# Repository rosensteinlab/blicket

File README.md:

### An Open-Source Blicket Detector for Cognitive Science Research

Hatem Mohamed<sup>1</sup>, Gabriella Modesti<sup>2</sup>, David M. Sobel<sup>2</sup>, and Jacob K. Rosenstein<sup>1</sup>

<sup>1</sup> School of Engineering, Brown University, Providence, RI

<sup>2</sup> Department of Cognitive and Psychological Sciences, Brown University, Providence, RI

This project presents a practical, reprogrammable Blicket Detector designed to support cognitive psychology experiments that investigate causal reasoning in young children. The device combines an Arduino-based microcontroller, an RF remote module, LED strips, switches, and a translucent window to deliver flexible, interactive feedback through light and sound. The design allows different behaviors—such as multi-color illumination and buzzer activation—to be easily reconfigured using existing Arduino libraries, making it simple to adapt to various experimental needs. Powered by a portable power bank, the system features a modular PCB layout that simplifies assembly and maintenance while keeping power consumption low. By providing an intuitive, hands-on way for children to explore cause-and-effect relationships, this Blicket Detector offers researchers a reliable, customizable platform for replicating and extending classic experiments on early cognitive development.

--------------------

All data, source code, and supporting files are available on the GitHub repository:
https://github.com/rosensteinlab/blicket 

If you use or refer to this design, please cite it as:

Hatem Mohamed, Gabriella Modesti, David M. Sobel, and Jacob K. Rosenstein. “An Open-Source Blicket Detector for Cognitive Science Research.” School of Engineering and Department of Cognitive and Psychological Sciences, Brown University, 2025. Available at: https://github.com/rosensteinlab/blicket. DOI: 10.5281/zenodo.15880720

--------------------

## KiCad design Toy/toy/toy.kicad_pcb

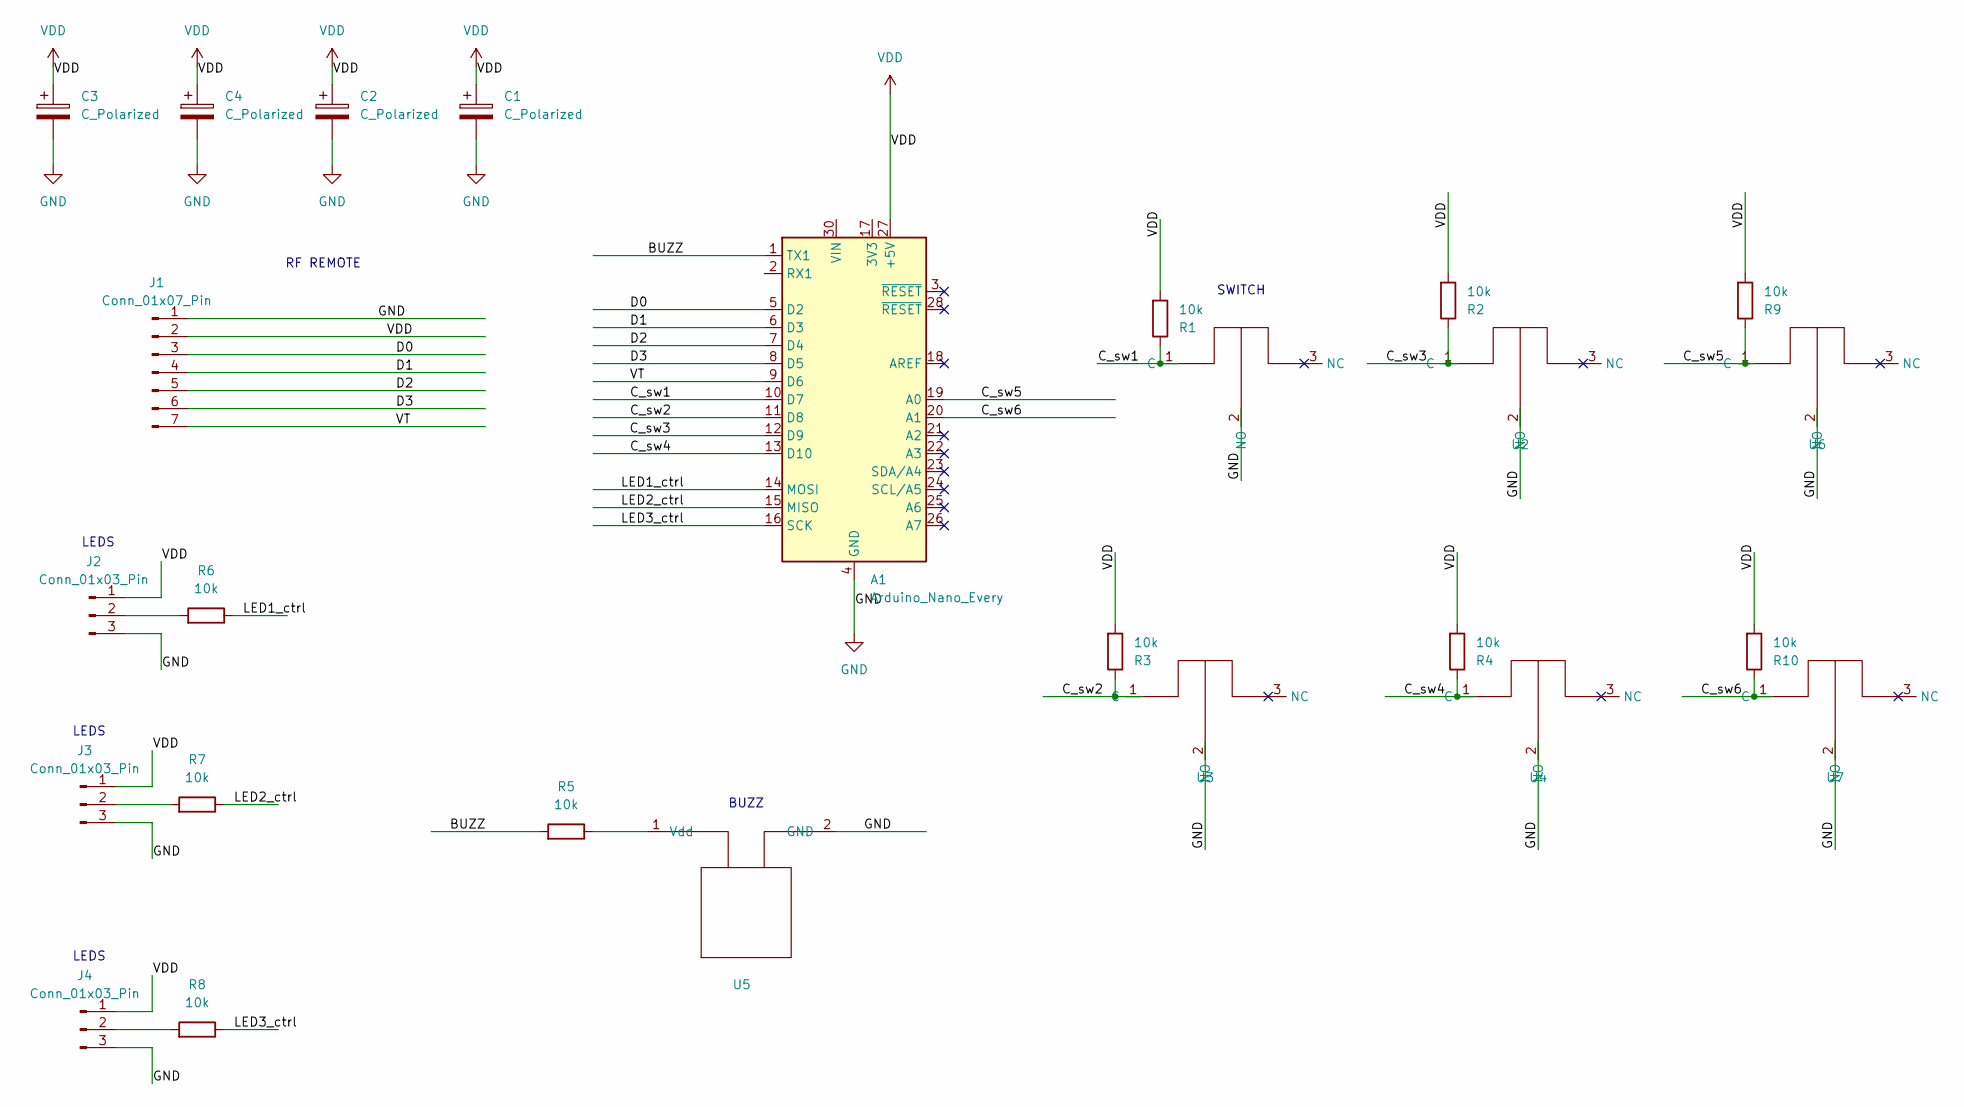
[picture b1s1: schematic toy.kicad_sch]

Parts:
A1: Arduino_Nano_Every; Arduino_Nano
C1, C2, C3, C4: C_Polarized; CP_Radial_Tantal_D5.5mm_P5.00mm
J1: Conn_01x07_Pin; PinSocket_1x07_P2.54mm_Vertical
J2, J3, J4: Conn_01x03_Pin; PinSocket_1x03_P2.54mm_Vertical
R1, R2, R3, R4, R5, R6, R7, R8, R9, R10: 10k; R_Axial_DIN0207_L6.3mm_D2.5mm_P10.16mm_Horizontal
U1, U2, U3, U4, U6, U7: switch
U5: PS1240

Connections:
/BUZZ: A1.1 (TX1), R5.2
/C_sw1: A1.10 (D7), R1.1, U1.1 (C)
/C_sw2: A1.11 (D8), R3.1, U3.1 (C)
/C_sw3: A1.12 (D9), R2.1, U2.1 (C)
/C_sw4: A1.13 (D10), R4.1, U4.1 (C)
/C_sw5: A1.19 (A0), R9.1, U6.1 (C)
/C_sw6: A1.20 (A1), R10.1, U7.1 (C)
/D0: A1.5 (D2), J1.3
/D1: A1.6 (D3), J1.4
/D2: A1.7 (D4), J1.5
/D3: A1.8 (D5), J1.6
/LED1_ctrl: A1.14 (MOSI), R6.1
/LED2_ctrl: A1.15 (MISO), R7.1
/LED3_ctrl: A1.16 (SCK), R8.1
/VT: A1.9 (D6), J1.7
GND: A1.4 (GND), A1.29 (GND), C1.2, C2.2, C3.2, C4.2, J1.1, J2.3, J3.3, J4.3, U1.2 (NO), U2.2 (NO), U3.2 (NO), U4.2 (NO), U5.2 (GND), U6.2 (NO), U7.2 (NO)
unnamed: J2.2, R6.2
unnamed: J3.2, R7.2
unnamed: J4.2, R8.2
unnamed: R5.1, U5.1 (Vdd)
VDD: A1.27 (+5V), C1.1, C2.1, C3.1, C4.1, J1.2, J2.1, J3.1, J4.1, R1.2, R2.2, R3.2, R4.2, R9.2, R10.2

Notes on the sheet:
LEDS
RF REMOTE
BUZZ
SWITCH

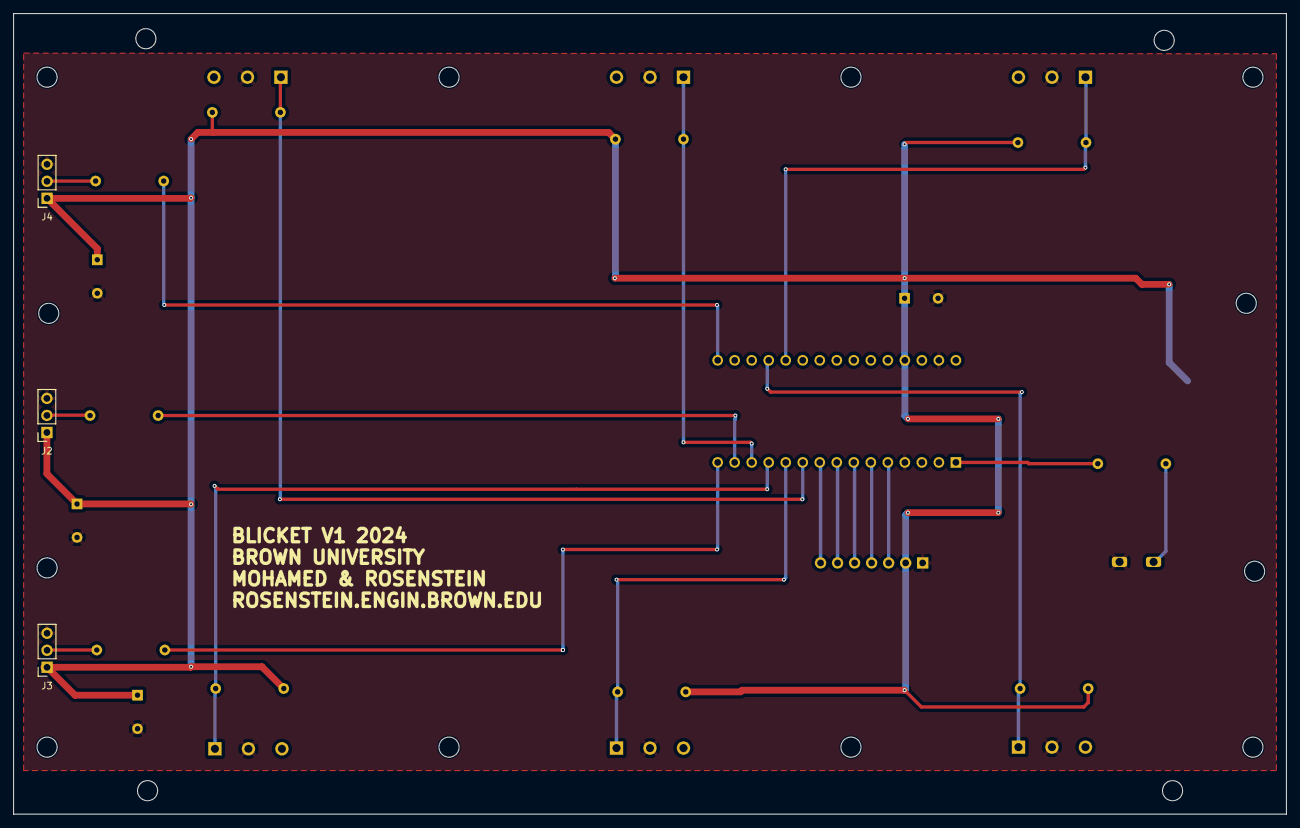
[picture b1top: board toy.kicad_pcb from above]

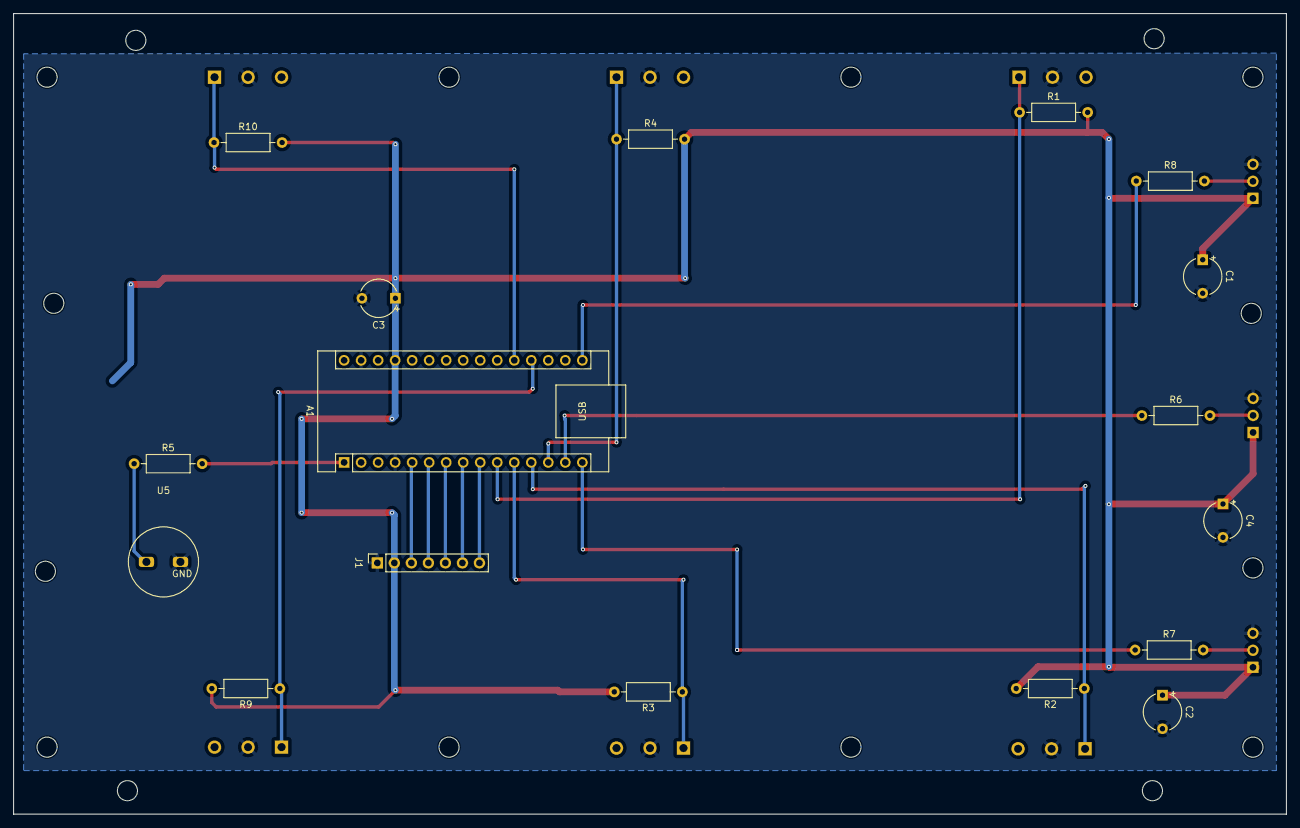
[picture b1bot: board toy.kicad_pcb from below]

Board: 2 copper layers, 190.0 x 119.5 mm, 26 parts (17 on the bottom side), 21 nets.

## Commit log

2024-10-24 added the project files
    "toy is the project" and the other folder is the footprint library, and the symbols
2024-10-31 Routed PCB
2024-10-31 V2
    resistors changed
    routing strategy
    added more leds
2024-10-31 V2.1
    Ground fill added
2024-11-01 Led directionality altered
2024-11-01 V3.0
    Led orientation fixed, bigger ground fill
2024-11-03 PCB updates, change switches to SPST style
2024-11-03 PCB updates, move LEDs to same side; 6 switches; move standoff holes to edges
2025-07-11 updated blicket files
    fixed the distancing problem
2025-07-11 updated+cleaned code
2025-07-11 Create LICENSE
2025-07-13 create gitignore
